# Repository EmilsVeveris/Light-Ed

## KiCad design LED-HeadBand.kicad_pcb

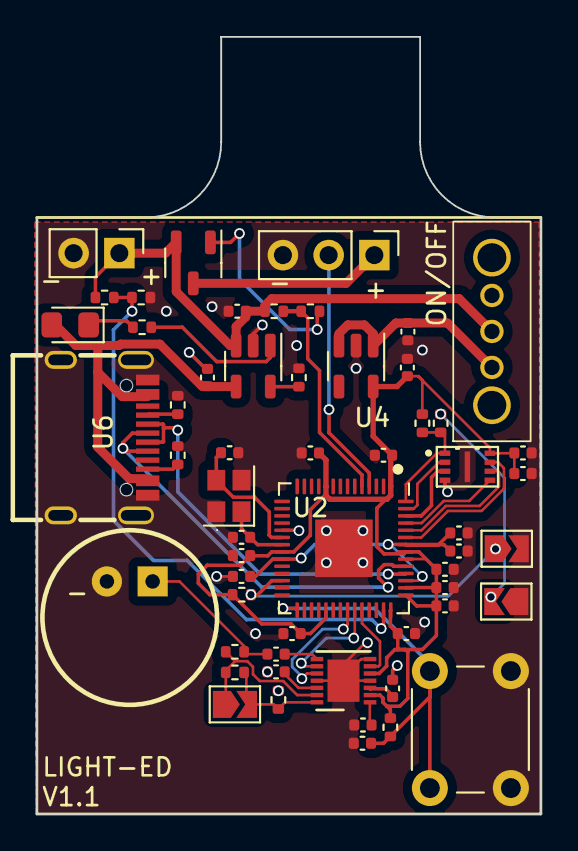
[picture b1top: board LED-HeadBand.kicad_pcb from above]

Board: 2 copper layers, 28.0 x 43.2 mm, 56 parts (0 on the bottom side), 39 nets.

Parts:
BT1: Battery; PinHeader_1x02_P2.54mm_Vertical
C1, C2, C3, C4, C5, C6, C7, C8, C11, C15, C19, C23, C24: 100 nF; C_0402_1005Metric
C9, C10, C12, C16: 2.2 uF; C_0402_1005Metric
C13, C14: 8 pF; C_0402_1005Metric
C17: 0.47 uF; C_0402_1005Metric
C18, C20: 1 uF; C_0402_1005Metric
C21, C22: 4.7 uF; C_0402_1005Metric
D1: LED; D_0805_2012Metric_Pad1.15x1.40mm_HandSolder
J2: Screw_Terminal_01x03; PinHeader_1x03_P2.54mm_Vertical
JP1, JP2, JP3: SolderJumper_2_Open; SolderJumper-2_P1.3mm_Open_TrianglePad1.0x1.5mm
Q1: PMOS; SOT-23-3
R1: 2.2k; R_0402_1005Metric
R2: 150k; R_0402_1005Metric
R3, R14: 100k; R_0402_1005Metric
R4: 2k; R_0402_1005Metric
R5, R11: 300; R_0402_1005Metric
R6, R7: 5.1k; R_0402_1005Metric
R8, R10, R12, R15: 10k; R_0402_1005Metric
R9: 1k; R_0402_1005Metric
R13: 50k; R_0402_1005Metric
SW1: Mode_Switch; SW_PUSH_6mm_H13mm
SW2: SW_DPDT_x2; OS102011MS2QS1
U1: MAX9814; DFN-14-1EP_3x3mm_P0.4mm_EP1.78x2.35mm
U2: RP2040; QFN-56-1EP_7x7mm_P0.4mm_EP3.2x3.2mm
U3: W25Q16JVUXIQ_TR; IC_W25Q16JVUXIQ_TR
U4: MIC5504-3.3YM5; SOT-23-5
U5: MCP73831-2-OT; SOT-23-5
U6: KH-TYPE-C-16P; USB-C-SMD_KH-TYPE-C-16P
U7: GMI9767P-46DB; MIC-TH_BD9.7-P2.54-D0.8-L-FD
Y1: 12 MHz; Crystal_SMD_2520-4Pin_2.5x2.0mm

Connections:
+3.3V: C1.2, C2.2, C3.2, C4.2, C5.2, C6.2, C10.2, C11.2, C12.2, C18.1, C24.2, R8.1, R10.1, R15.2, U1.2 (~SHDN), U1.5 (VDD), U2.1 (IOVDD), U2.10 (IOVDD), U2.22 (IOVDD), U2.33 (IOVDD), U2.42 (IOVDD), U2.43 (ADC_AVDD), U2.44 (VREG_IN), U2.48 (USB_VDD), U2.49 (IOVDD), U3.8 (VCC), U4.5 (VOUT)
+5V: C22.1, D1.2 (A), U5.4 (V_{DD}), U6.A4 (VBUS), U6.A9 (VBUS), U6.B4 (VBUS), U6.B9 (VBUS)
+BATT: BT1.1 (+), C21.1, Q1.2 (S), R12.2, R13.1, SW2.2 (B), U5.3 (V_{BAT})
/A/R: U1.9 (A/R), U2.37 (GPIO25)
/BAT_VOL: R13.2, R14.1, U2.41 (GPIO29_ADC3)
/Diode_Cont: J2.2, U2.4 (GPIO2)
/Diode_power: J2.1, Q1.3 (D)
/GAIN: U1.10 (GAIN), U2.36 (GPIO24)
/MICBIAS: JP1.1 (A), R1.2, R2.1, U1.13 (MICBIAS)
/MICIN: C19.2, U1.8 (MICIN)
/MICOUT: U1.6 (MICOUT), U2.38 (GPIO26_ADC0)
/MOSFET_Controll: R11.1, R12.1, U2.5 (GPIO3)
/Mode_Switch: C23.1, R15.1, SW1.1, U2.29 (GPIO18)
/QSPI_SCLK: U2.52 (QSPI_SCLK), U3.6 (CLK)
/QSPI_SD0: U2.53 (QSPI_SD0), U3.5 (DI/IO0)
/QSPI_SD1: U2.55 (QSPI_SD1), U3.2 (DO/IO1)
/QSPI_SD2: U2.54 (QSPI_SD2), U3.3 (~WP/IO2)
/QSPI_SD3: U2.51 (QSPI_SD3), U3.7 (~HOLD/~RESET/IO3)
/QSPI_SS: R9.2, R10.2, U2.56 (QSPI_SS), U3.1 (~CS)
/TH: JP1.2 (B), R2.2, R3.1, U1.14 (TH)
/USB_DM: U2.46 (USB_DM), U6.A7 (DN1), U6.B7 (DN2)
/USB_DP: U2.47 (USB_DP), U6.A6 (DP1), U6.B6 (DP2)
GND: BT1.2 (-), C1.1, C2.1, C3.1, C4.1, C5.1, C6.1, C7.1, C8.1, C9.1, C10.1, C11.1, C12.1, C13.1, C14.1, C15.1, C16.1, C17.1, C18.2, C20.2, C21.2, C22.2, C23.2, C24.1, J2.3, JP2.2 (B), JP3.1 (A), R3.2, R4.2, R6.2, R7.2, R14.2, SW1.2, U1.4 (GND), U1.7 (GND), U1.11 (GND), U1.15 (GND), U2.19 (TESTEN), U2.57 (GND), U3.4 (GND), U3.9 (EXP), U4.2 (GND), U5.2 (V_{SS}), U6.1 (EP), U6.2 (EP), U6.3 (EP), U6.4 (EP), U6.A1 (GND), U6.A12 (GND), U6.B1 (GND), U6.B12 (GND), U7.2, Y1.2, Y1.4
unnamed: C19.1, R1.1, U7.1
unnamed: D1.1 (K), R5.2
unnamed: JP2.1 (A), R8.2, U2.26 (RUN)
unnamed: JP3.2 (B), R9.1
unnamed: Q1.1 (G), R11.2
unnamed: C20.1, SW2.1 (A), U4.1 (VIN), U4.3 (EN)
unnamed: C17.2, U1.12 (BIAS)
unnamed: C16.2, U1.3 (CG)
unnamed: C15.2, U1.1 (CT)
unnamed: C7.2, C8.2, C9.2, U2.23 (DVDD), U2.45 (VREG_VOUT), U2.50 (DVDD)
unnamed: C13.2, U2.20 (XIN), Y1.3
unnamed: C14.2, U2.21 (XOUT), Y1.1
unnamed: R4.1, U5.5 (PROG)
unnamed: R5.1, U5.1 (STAT)
unnamed: R6.1, U6.A5 (CC1)
unnamed: R7.1, U6.B5 (CC2)

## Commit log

2024-09-29 First commit Light-Ed V1.1
2024-09-29 Saved the file
2024-10-01 Kristers man lika mainīt lietas
2024-10-01 Updated GRB files
